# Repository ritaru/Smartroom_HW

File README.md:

# ATmega256RFR2 Zigbee Board & Firmware

## Development board specs

- 50mm x 50mm 1.6T FR-4 1oz Copper
- microUSB port for power input
- Integrated 3.3v regulator(IL1117-3.3)
- Overcurrent and overvoltage protection(PTC, TVS diode)
- GPIOs are populated by port indexes
- ISP Connector(10-pin) for programming
- ATmega64/128/256RFR2 compatible
- All resistors, inductors, capacitors are 0603(1608 Metric) size.
- Antenna is connected to u.FL(IPEX) external connector
- The schematic is mostly like the datasheet's application note example.

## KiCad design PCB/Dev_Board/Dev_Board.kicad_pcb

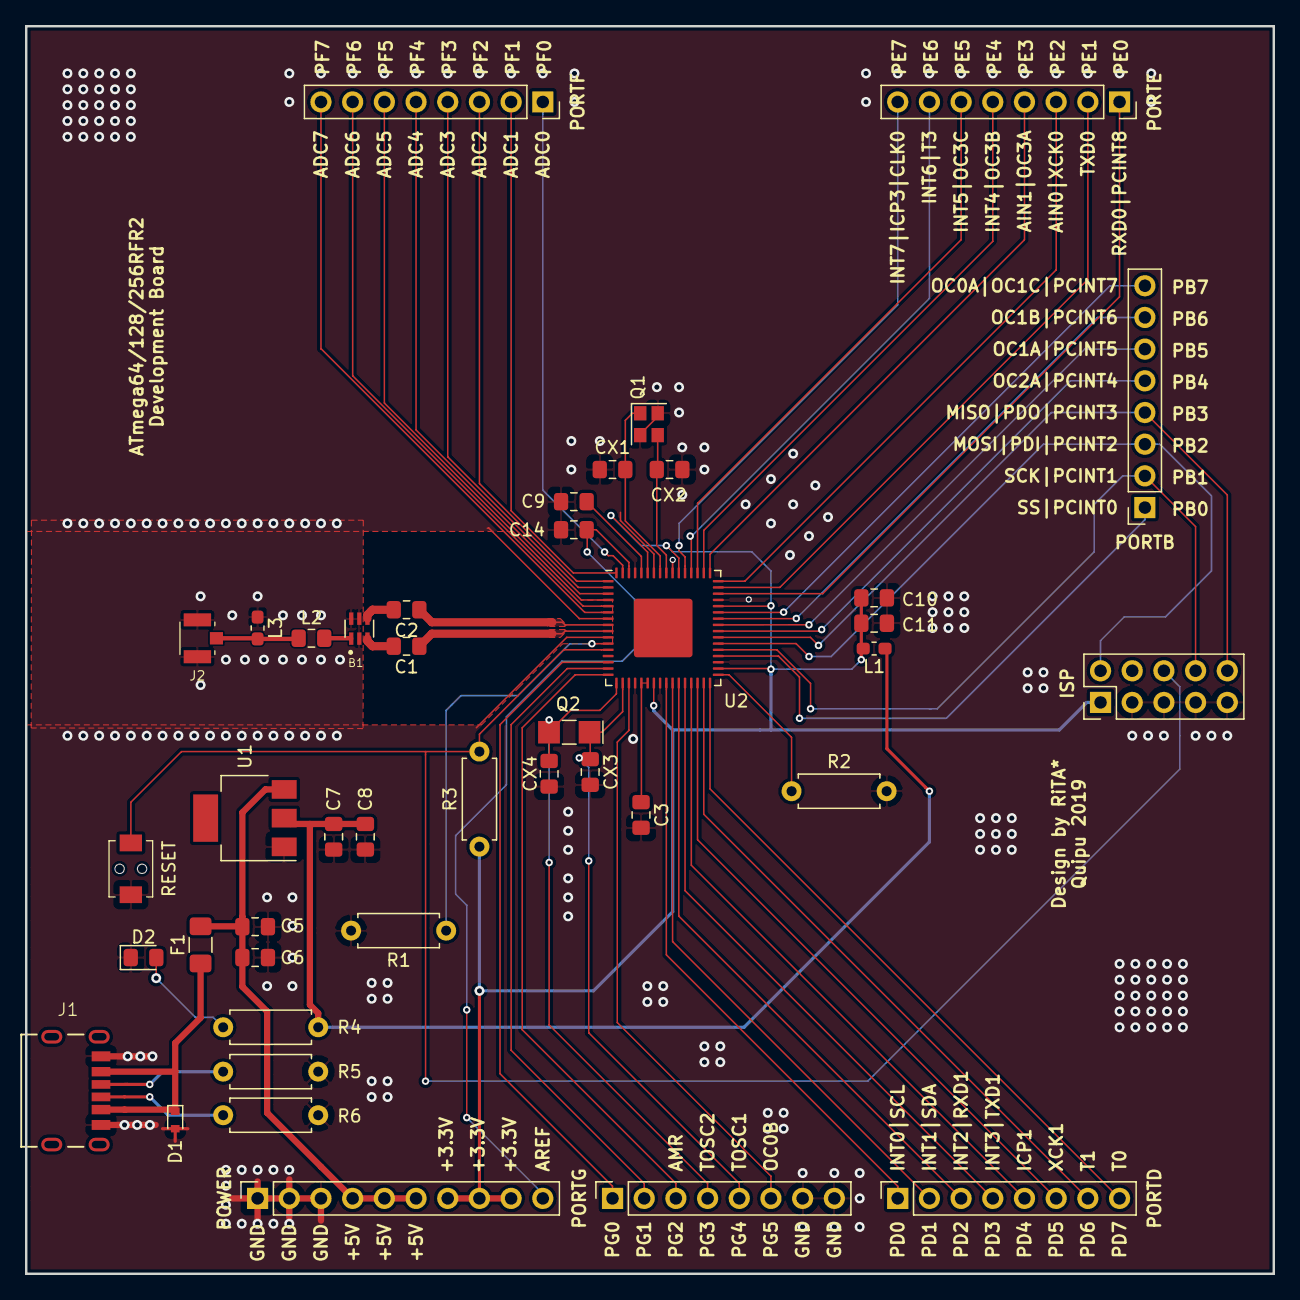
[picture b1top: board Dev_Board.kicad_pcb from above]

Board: 2 copper layers, 100.0 x 100.0 mm, 42 parts (0 on the bottom side), 60 nets.

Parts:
B1: BALUN0805; 2450BM15A0015E
C1, C2: 22p; C_0805_2012Metric_Pad1.15x1.40mm_HandSolder
C3, C9: 1u; C_0805_2012Metric_Pad1.15x1.40mm_HandSolder
C5, C7: 4.7u; C_0805_2012Metric_Pad1.15x1.40mm_HandSolder
C6, C8, C10, C11, C14: 100n; C_0805_2012Metric_Pad1.15x1.40mm_HandSolder
CX1, CX2, CX3, CX4: 12p; C_0805_2012Metric_Pad1.15x1.40mm_HandSolder
D1: CESD5V0D5; D_SOD-523
D2: E6C0603URAC1UDA; LED_0805_2012Metric_Pad1.15x1.40mm_HandSolder
F1: MF-NSMF110-2; Fuse_1206_3216Metric_Pad1.42x1.75mm_HandSolder
ISP1: Conn_02x05_Odd_Even; PinHeader_2x05_P2.54mm_Vertical
J1: TYPE-C-31-M-17
J2: Conn_Coaxial; U.FL
L1: BLM18BB221SN1D; L_0603_1608Metric_Pad1.05x0.95mm_HandSolder
L2: Balancing; L_0805_2012Metric_Pad1.15x1.40mm_HandSolder
L3: Balancing; L_0603_1608Metric_Pad1.05x0.95mm_HandSolder
PORTB1: Conn_01x08; PinSocket_1x08_P2.54mm_Vertical
PORTD1: Conn_01x08; PinSocket_1x08_P2.54mm_Vertical
PORTE1: Conn_01x08; PinSocket_1x08_P2.54mm_Vertical
PORTF1: Conn_01x08; PinSocket_1x08_P2.54mm_Vertical
PORTG1: Conn_01x08; PinSocket_1x08_P2.54mm_Vertical
POWER1: Conn_01x10; PinSocket_1x10_P2.54mm_Vertical
Q1: 16M; Crystal_SMD_2520-4Pin_2.5x2.0mm
Q2: 32.768k; Crystal_SMD_EuroQuartz_EQ161-2Pin_3.2x1.5mm_HandSoldering
R1, R2: 10k; R_Axial_DIN0207_L6.3mm_D2.5mm_P7.62mm_Horizontal
R3: 100k; R_Axial_DIN0207_L6.3mm_D2.5mm_P7.62mm_Horizontal
R4: 56R; R_Axial_DIN0207_L6.3mm_D2.5mm_P7.62mm_Horizontal
R5, R6: 5.1k; R_Axial_DIN0207_L6.3mm_D2.5mm_P7.62mm_Horizontal
SW1: K2-1807SA-B4DW-06
U1: AMS1117-3.3; SOT-223-3_TabPin2
U2: ATmega256RFR2; QFN-64-1EP_9x9mm_P0.5mm_EP4.7x4.7mm

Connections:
+3V3: C10.1, C11.1, ISP1.1, L1.2, POWER1.7, POWER1.8, POWER1.9, R3.1, U2.23, U2.34, U2.44, U2.54, U2.59
+5V: D1.1, F1.1, J1.VBUS
+VDC: C5.1, C6.1, F1.2, POWER1.4, POWER1.5, POWER1.6, U1.3
AREF: C14.1, POWER1.10, U2.62
GND: B1.GND, C3.2, C5.2, C6.2, C7.2, C8.2, C9.2, C10.2, C11.2, C14.2, CX1.2, CX2.2, CX3.2, CX4.2, D1.2, D2.1, ISP1.3, ISP1.5, ISP1.7, ISP1.9, J1.GND, J2.2, L3.1, PORTG1.7, PORTG1.8, POWER1.1, POWER1.2, POWER1.3, Q1.2, Q1.4, R1.2, R2.2, R5.1, R6.1, SW1.2, U1.1, U2.7, U2.10, U2.20, U2.24, U2.35, U2.45, U2.55, U2.58, U2.61
MISO: ISP1.10, PORTB1.4, U2.39
MOSI: ISP1.2, PORTB1.3, U2.38
unnamed: B1.BAL1, C1.2
unnamed: B1.BAL2, C2.2
unnamed: B1.UNBAL, L2.2
unnamed: C3.1, U2.21, U2.22
unnamed: C7.1, C8.1, L1.1, R4.1, U1.2
unnamed: C9.1, U2.60
unnamed: D2.2, R4.2
unnamed: J1.CC1, R5.2
unnamed: J1.CC2, R6.2
unnamed: J2.1, L2.1, L3.2
unnamed: PORTB1.1, U2.36
unnamed: PORTB1.5, U2.40
unnamed: PORTB1.6, U2.41
unnamed: PORTB1.7, U2.42
unnamed: PORTB1.8, U2.43
unnamed: PORTD1.1, U2.25
unnamed: PORTD1.2, U2.26
unnamed: PORTD1.3, U2.27
unnamed: PORTD1.4, U2.28
unnamed: PORTD1.5, U2.29
unnamed: PORTD1.6, U2.30
unnamed: PORTD1.7, U2.31
unnamed: PORTD1.8, U2.32
unnamed: PORTE1.1, U2.46
unnamed: PORTE1.2, U2.47
unnamed: PORTE1.3, U2.48
unnamed: PORTE1.4, U2.49
unnamed: PORTE1.5, U2.50
unnamed: PORTE1.6, U2.51
unnamed: PORTE1.7, U2.52
unnamed: PORTE1.8, U2.53
unnamed: PORTF1.1, U2.63
unnamed: PORTF1.2, U2.64
unnamed: PORTF1.3, U2.1
unnamed: PORTF1.4, U2.2
unnamed: PORTF1.5, U2.3
unnamed: PORTF1.6, U2.4
unnamed: PORTF1.7, U2.5
unnamed: PORTF1.8, U2.6
unnamed: PORTG1.1, U2.14
unnamed: PORTG1.2, U2.15
unnamed: PORTG1.3, U2.16
unnamed: PORTG1.6, U2.19
unnamed: R1.1, U2.11
unnamed: R2.1, U2.33
RF_N: C1.1, U2.9
RF_P: C2.1, U2.8
SCK: ISP1.8, PORTB1.2, U2.37
TOSC1: CX3.1, PORTG1.5, Q2.1, U2.18
TOSC2: CX4.1, PORTG1.4, Q2.2, U2.17
XTAL1: CX1.1, Q1.1, U2.57
XTAL2: CX2.1, Q1.3, U2.56
~RST: ISP1.6, R3.2, SW1.1, U2.12

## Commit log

2019-09-20 Fixed L1 power net
    Also added a power indicator LED
2019-09-23 Board design almost done
    some parts need to be replaced with larger footprints(fuse, caps, etc...)
    I haven't done the RF side yet.
    Also, I changed the switch to similarly designed one that had more detailed dimensions.
2019-10-05 Final PCB design
